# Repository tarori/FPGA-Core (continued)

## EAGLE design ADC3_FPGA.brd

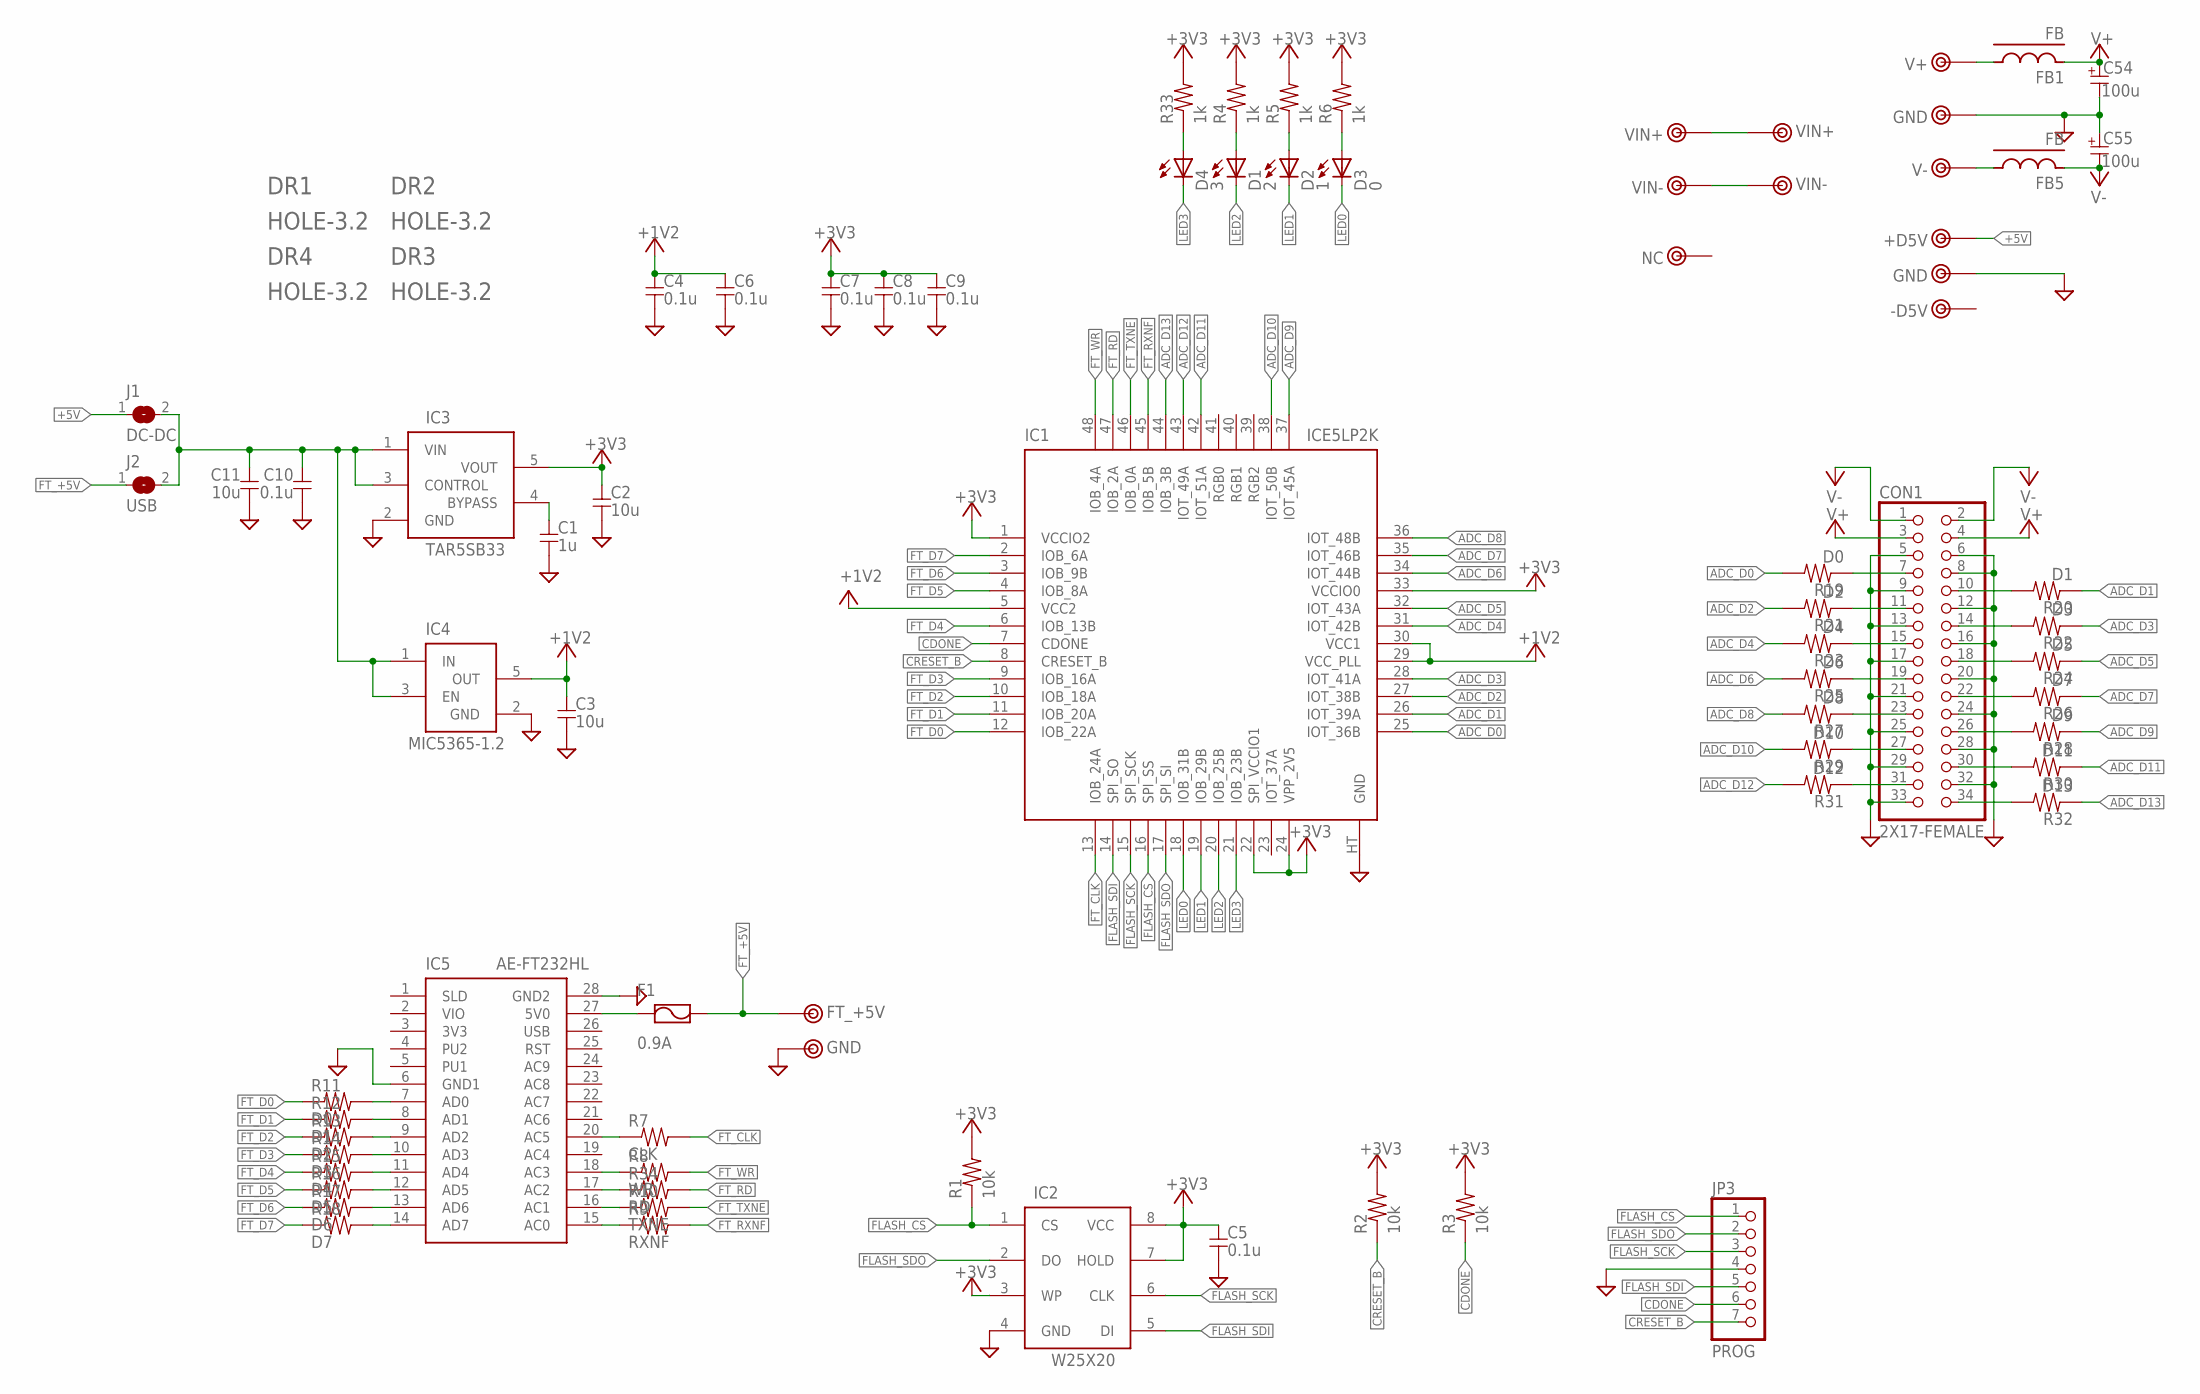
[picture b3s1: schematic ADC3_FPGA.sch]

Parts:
C1: 1u; 1608
C2, C3: 10u; 2012
C4, C5, C6, C7, C8, C9, C10: 0.1u; 1608
C11: 10u; 3216
C54, C55: 100u; E2,5-8
CON1: 2X17-FEMALE; 2X17/90
D1: 2; D1608
D2: 1; D1608
D3: 0; D1608
D4: 3; D1608
DR1, DR2, DR3, DR4: HOLE-3.2; HOLE_3.2
F1: 0.9A; 3216
FB1, FB5: FB; 2012-J
IC1: ICE5LP2K; QFN48HT
IC2: W25X20; SOP8
IC3: TAR5SB33; SOT23-5
IC4: MIC5365-1.2; SC70
IC5: AE-FT232HL
J1: DC-DC; 2012-J
J2: USB; 2012-J
JP3: PROG; 1X07
R1, R2, R3: 10k; 1608
R4, R5, R6, R33: 1k; 1608
R7: CLK; 1608-J
R8: WR; 1608-J
R9: RXNF; 1608-J
R10: TXNE; 1608-J
R11, R19: D0; 1608-J
R12, R20: D1; 1608-J
R13, R21: D2; 1608-J
R14, R22: D3; 1608-J
R15, R23: D4; 1608-J
R16, R24: D5; 1608-J
R17, R25: D6; 1608-J
R18, R26: D7; 1608-J
R27: D8; 1608-J
R28: D9; 1608-J
R29: D10; 1608-J
R30: D11; 1608-J
R31: D12; 1608-J
R32: D13; 1608-J
R34: RD; 1608-J
TP1: +D5V; TESTPIN
TP2: NC; TESTPIN
TP3, TP5, TP18: GND; TESTPIN
TP4: FT_+5V; TESTPIN
TP15: -D5V; TESTPIN
TP17: V+; TESTPIN
TP19: V-; TESTPIN
TP21, TP30: VIN+; TESTPIN
TP22, TP31: VIN-; TESTPIN

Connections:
+1V2: C3.1, C4.1, C6.1, IC1.5 (VCC2), IC1.29 (VCC_PLL), IC1.30 (VCC1), IC4.5 (OUT)
+3V3: C2.1, C5.1, C7.1, C8.1, C9.1, IC1.1 (VCCIO2), IC1.22 (SPI_VCCIO1), IC1.24 (VPP_2V5), IC1.33 (VCCIO0), IC2.3 (WP), IC2.7 (HOLD), IC2.8 (VCC), IC3.5 (VOUT), R1.2, R2.2, R3.2, R4.2, R5.2, R6.2, R33.2
+5V: J1.1, TP1.1
ADC_D0: IC1.25 (IOT_36B), R19.2
ADC_D1: IC1.26 (IOT_39A), R20.1
ADC_D2: IC1.27 (IOT_38B), R21.2
ADC_D3: IC1.28 (IOT_41A), R22.1
ADC_D4: IC1.31 (IOT_42B), R23.2
ADC_D5: IC1.32 (IOT_43A), R24.1
ADC_D6: IC1.34 (IOT_44B), R25.2
ADC_D7: IC1.35 (IOT_46B), R26.1
ADC_D8: IC1.36 (IOT_48B), R27.2
ADC_D9: IC1.37 (IOT_45A), R28.1
ADC_D10: IC1.38 (IOT_50B), R29.2
ADC_D11: IC1.42 (IOT_51A), R30.1
ADC_D12: IC1.43 (IOT_49A), R31.2
ADC_D13: IC1.44 (IOB_3B), R32.1
CDONE: IC1.7 (CDONE), JP3.6, R3.1
CRESET_B: IC1.8 (CRESET_B), JP3.7, R2.1
FLASH_CS: IC1.16 (SPI_SS), IC2.1 (CS), JP3.1, R1.1
FLASH_SCK: IC1.15 (SPI_SCK), IC2.6 (CLK), JP3.3
FLASH_SDI: IC1.14 (SPI_SO), IC2.5 (DI), JP3.5
FLASH_SDO: IC1.17 (SPI_SI), IC2.2 (DO), JP3.2
FT_+5V: F1.2, J2.1, TP4.1
FT_CLK: IC1.13 (IOB_24A), R7.2
FT_D0: IC1.12 (IOB_22A), R11.1
FT_D1: IC1.11 (IOB_20A), R12.1
FT_D2: IC1.10 (IOB_18A), R13.1
FT_D3: IC1.9 (IOB_16A), R14.1
FT_D4: IC1.6 (IOB_13B), R15.1
FT_D5: IC1.4 (IOB_8A), R16.1
FT_D6: IC1.3 (IOB_9B), R17.1
FT_D7: IC1.2 (IOB_6A), R18.1
FT_RD: IC1.47 (IOB_2A), R34.2
FT_RXNF: IC1.45 (IOB_5B), R9.2
FT_TXNE: IC1.46 (IOB_0A), R10.2
FT_WR: IC1.48 (IOB_4A), R8.2
GND: C1.2, C2.2, C3.2, C4.2, C5.2, C6.2, C7.2, C8.2, C9.2, C10.2, C11.2, C54.- (2), C55.+ (1), CON1.5, CON1.6, CON1.8, CON1.9, CON1.12, CON1.13, CON1.16, CON1.17, CON1.20, CON1.21, CON1.24, CON1.25, CON1.28, CON1.29, CON1.32, CON1.33, IC1.HT (GND), IC2.4 (GND), IC3.2 (GND), IC4.2 (GND), IC5.6 (GND1), IC5.28 (GND2), JP3.4, TP3.1, TP5.1, TP18.1
LED0: D3.K, IC1.18 (IOB_31B)
LED1: D2.K, IC1.19 (IOB_29B)
LED2: D1.K, IC1.20 (IOB_25B)
LED3: D4.K, IC1.21 (IOB_23B)
unnamed: C1.1, IC3.4 (BYPASS)
unnamed: IC5.15 (AC0), R9.1
unnamed: D4.A, R33.1
unnamed: IC5.16 (AC1), R10.1
unnamed: IC5.18 (AC3), R8.1
unnamed: IC5.20 (AC5), R7.1
unnamed: IC5.7 (AD0), R11.2
unnamed: IC5.8 (AD1), R12.2
unnamed: IC5.9 (AD2), R13.2
unnamed: IC5.10 (AD3), R14.2
unnamed: IC5.11 (AD4), R15.2
unnamed: IC5.12 (AD5), R16.2
unnamed: IC5.13 (AD6), R17.2
unnamed: IC5.14 (AD7), R18.2
unnamed: CON1.31, R31.1
unnamed: C10.1, C11.1, IC3.1 (VIN), IC3.3 (CONTROL), IC4.1 (IN), IC4.3 (EN), J1.2, J2.2
unnamed: CON1.27, R29.1
unnamed: CON1.23, R27.1
unnamed: CON1.19, R25.1
unnamed: CON1.15, R23.1
unnamed: IC5.17 (AC2), R34.1
unnamed: F1.1, IC5.27 (5V0)
unnamed: D1.A, R4.1
unnamed: D2.A, R5.1
unnamed: D3.A, R6.1
unnamed: CON1.11, R21.1
unnamed: CON1.7, R19.1
unnamed: CON1.10, R20.2
unnamed: CON1.14, R22.2
unnamed: CON1.18, R24.2
unnamed: CON1.22, R26.2
unnamed: CON1.26, R28.2
unnamed: CON1.30, R30.2
unnamed: CON1.34, R32.2
unnamed: FB1.1, TP17.1
unnamed: FB5.1, TP19.1
unnamed: TP21.1, TP30.1
unnamed: TP22.1, TP31.1
V+: C54.+ (1), CON1.3, CON1.4, FB1.2
V-: C55.- (2), CON1.1, CON1.2, FB5.2

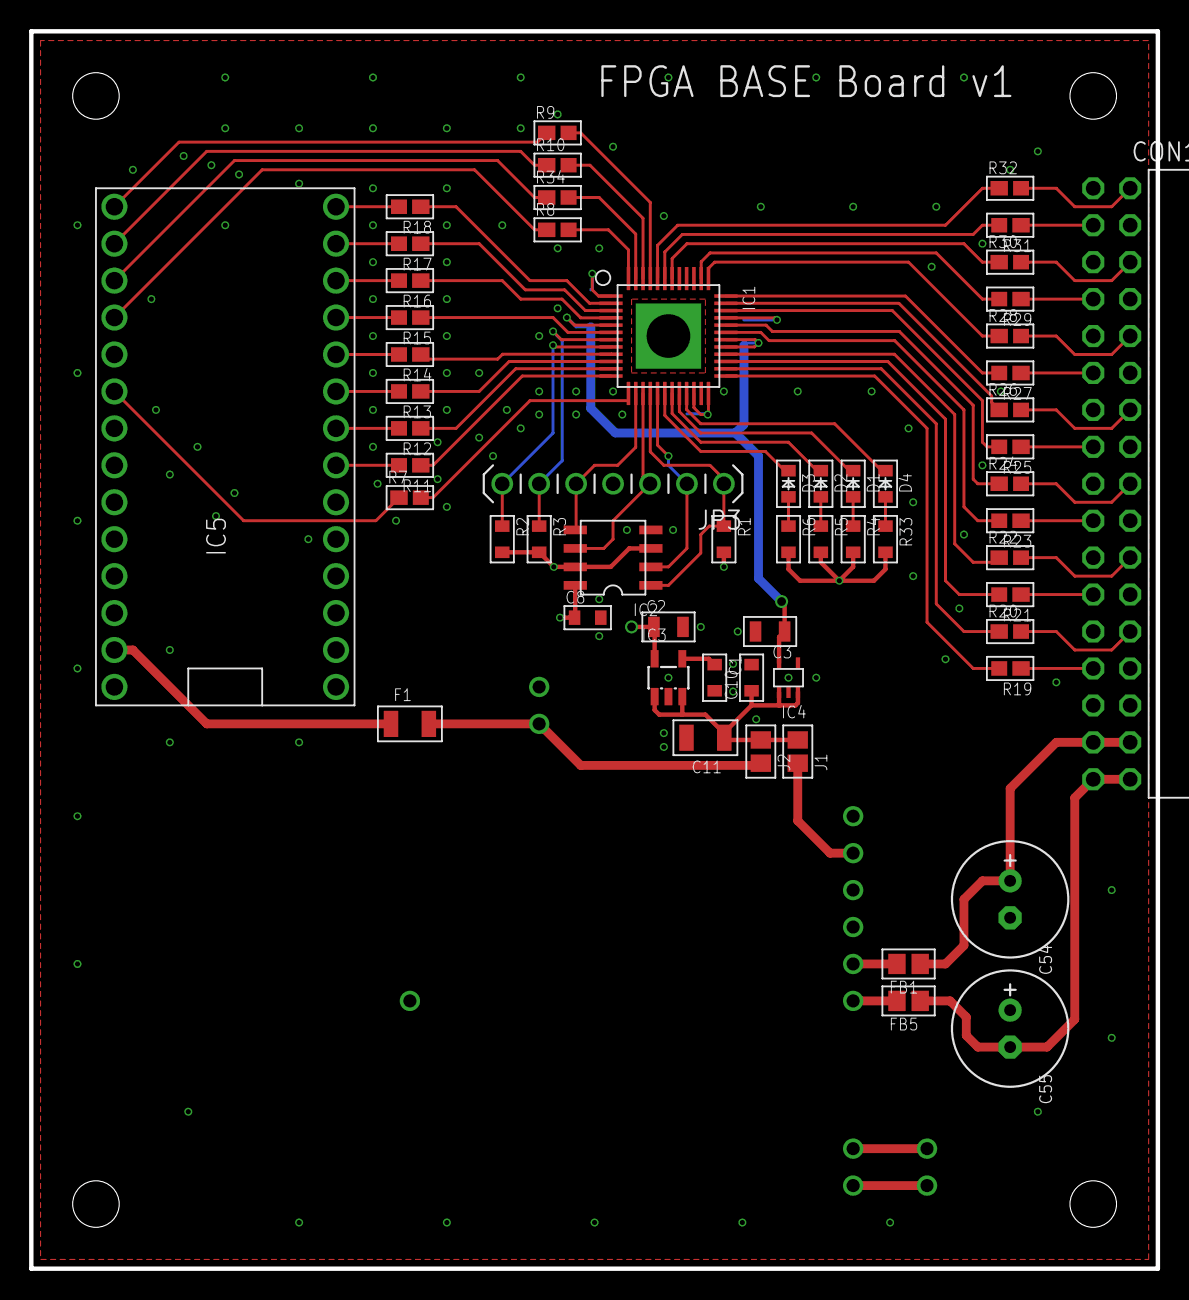
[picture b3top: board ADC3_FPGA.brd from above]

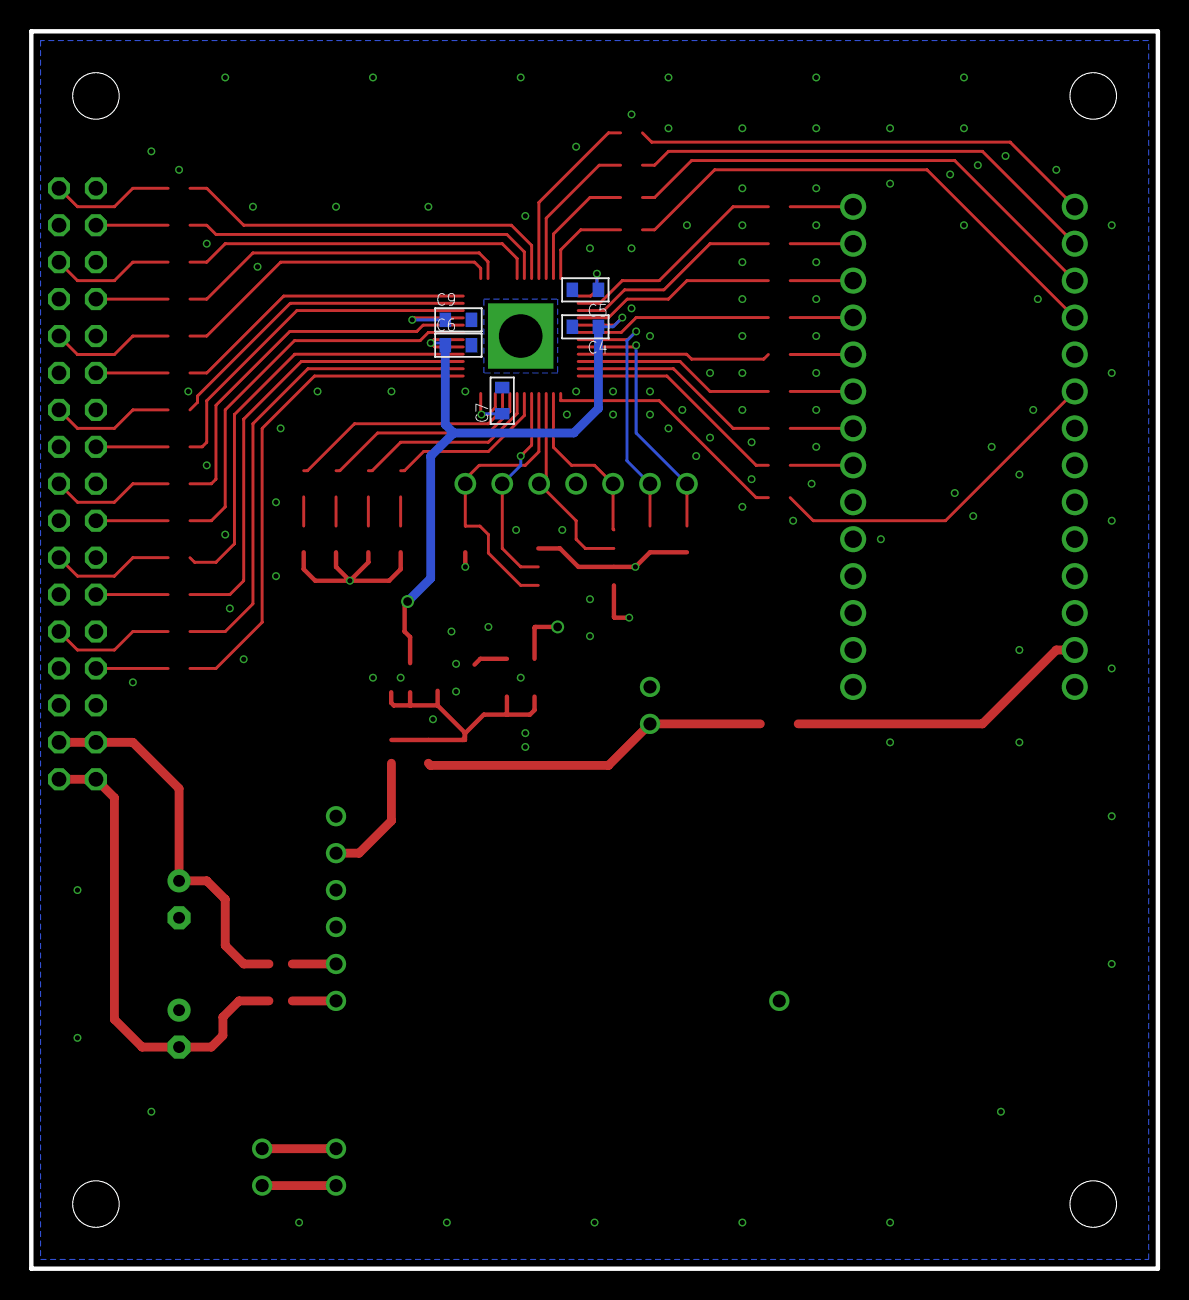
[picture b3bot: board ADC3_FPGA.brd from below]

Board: 4 copper layers, 77.5 x 85.1 mm, 80 parts (5 on the bottom side), 82 nets.

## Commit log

2023-04-18 ver1
2023-04-20 こんな感じ
2023-06-03 メザニンコネクタ
2023-06-09 4層DRC
2023-06-30 コネクタをピン名に変更
2023-06-30 FT2232のEEPROMの配線を修正
2023-07-04 古いファイルを削除
2023-07-09 intel
2023-07-16 Artix-7 途中
2023-07-16 via打てば終わり
2023-07-29 OSCを追加して再発注
2024-06-15 Type-C
2024-06-30 長穴修正
